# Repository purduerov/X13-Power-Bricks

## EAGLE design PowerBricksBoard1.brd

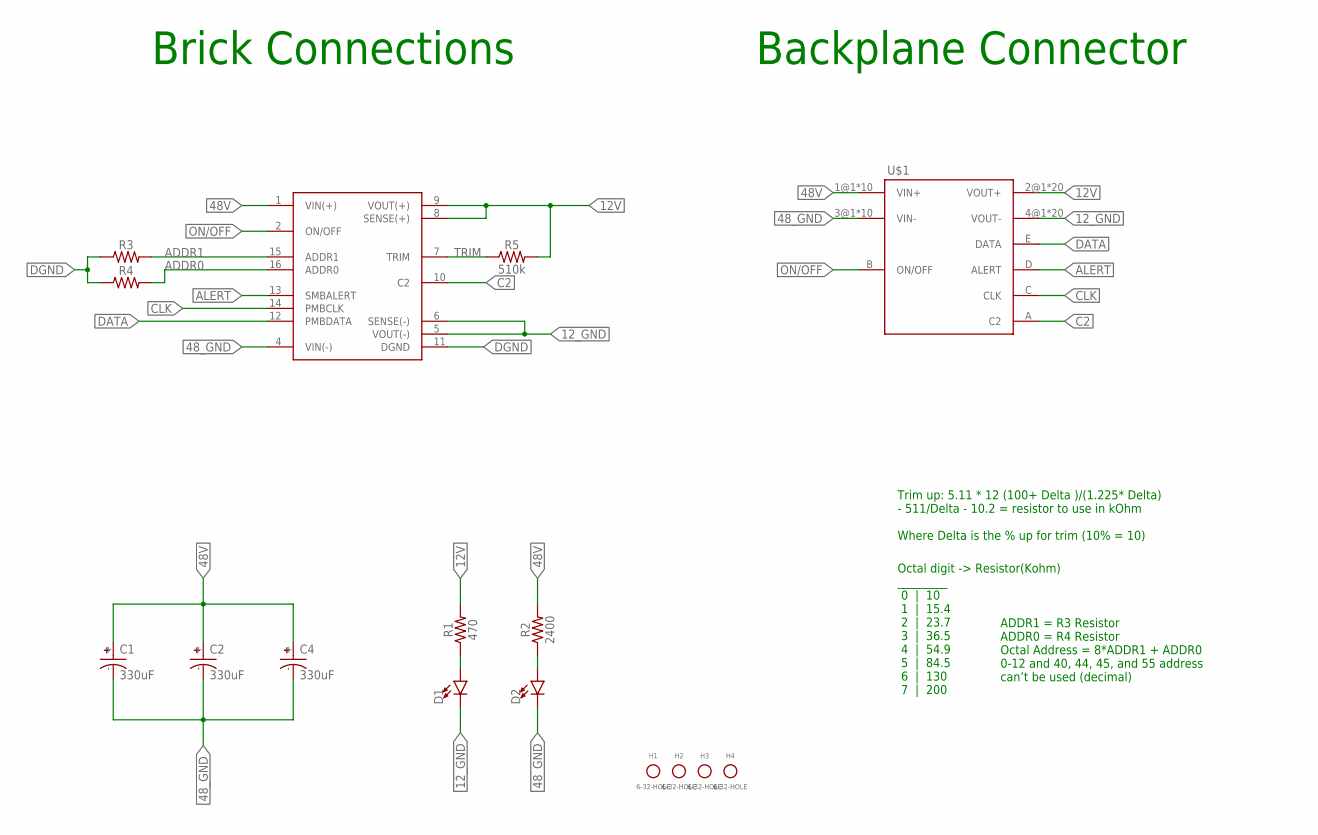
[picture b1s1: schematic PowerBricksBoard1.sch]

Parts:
C1, C2, C4: 330uF; CAPAE1030X1050N
D1, D2: LED0603; LED-0603
H1, H2, H3, H4: 6-32-HOLE
R1: 470; 0603
R2: 2400; 0603
R3, R4: 0603
R5: 510k; 0603
U$1: BRICK2DIST; BRICK2DIST_D2
U$2: Q48SC12050NRDH

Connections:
12V: R1.2, R5.2, U$1.2@1 (VOUT+), U$1.2@2 (VOUT+), U$1.2@3 (VOUT+), U$1.2@4 (VOUT+), U$1.2@5 (VOUT+), U$1.2@6 (VOUT+), U$1.2@7 (VOUT+), U$1.2@8 (VOUT+), U$1.2@9 (VOUT+), U$1.2@10 (VOUT+), U$1.2@11 (VOUT+), U$1.2@12 (VOUT+), U$1.2@13 (VOUT+), U$1.2@14 (VOUT+), U$1.2@15 (VOUT+), U$1.2@16 (VOUT+), U$1.2@17 (VOUT+), U$1.2@18 (VOUT+), U$1.2@19 (VOUT+), U$1.2@20 (VOUT+), U$2.8 (SENSE(+)), U$2.9 (VOUT(+))
12_GND: D1.C, U$1.4@1 (VOUT-), U$1.4@2 (VOUT-), U$1.4@3 (VOUT-), U$1.4@4 (VOUT-), U$1.4@5 (VOUT-), U$1.4@6 (VOUT-), U$1.4@7 (VOUT-), U$1.4@8 (VOUT-), U$1.4@9 (VOUT-), U$1.4@10 (VOUT-), U$1.4@11 (VOUT-), U$1.4@12 (VOUT-), U$1.4@13 (VOUT-), U$1.4@14 (VOUT-), U$1.4@15 (VOUT-), U$1.4@16 (VOUT-), U$1.4@17 (VOUT-), U$1.4@18 (VOUT-), U$1.4@19 (VOUT-), U$1.4@20 (VOUT-), U$2.5 (VOUT(-)), U$2.6 (SENSE(-))
48V: C1.+, C2.+, C4.+, R2.2, U$1.1@1 (VIN+), U$1.1@2 (VIN+), U$1.1@3 (VIN+), U$1.1@4 (VIN+), U$1.1@5 (VIN+), U$1.1@6 (VIN+), U$1.1@7 (VIN+), U$1.1@8 (VIN+), U$1.1@9 (VIN+), U$1.1@10 (VIN+), U$2.1 (VIN(+))
48_GND: C1.-, C2.-, C4.-, D2.C, U$1.3@1 (VIN-), U$1.3@2 (VIN-), U$1.3@3 (VIN-), U$1.3@4 (VIN-), U$1.3@5 (VIN-), U$1.3@6 (VIN-), U$1.3@7 (VIN-), U$1.3@8 (VIN-), U$1.3@9 (VIN-), U$1.3@10 (VIN-), U$2.4 (VIN(-))
ADDR0: R4.2, U$2.16 (ADDR0)
ADDR1: R3.2, U$2.15 (ADDR1)
ALERT: U$1.D (ALERT), U$2.13 (SMBALERT)
C2: U$1.A (C2), U$2.10 (C2)
CLK: U$1.C (CLK), U$2.14 (PMBCLK)
DATA: U$1.E (DATA), U$2.12 (PMBDATA)
DGND: R3.1, R4.1, U$2.11 (DGND)
unnamed: D1.A, R1.1
unnamed: D2.A, R2.1
ON/OFF: U$1.B (ON/OFF), U$2.2 (ON/OFF)
TRIM: R5.1, U$2.7 (TRIM)

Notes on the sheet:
Octal digit -> Resistor(Kohm) _________ 0 | 10 1 | 15.4 2 | 23.7 3 | 36.5 4 | 54.9 5 | 84.5 6 | 130 7 | 200
ADDR1 = R3 Resistor ADDR0 = R4 Resistor Octal Address = 8*ADDR1 + ADDR0 0-12 and 40, 44, 45, and 55 address can’t be used (decimal)
Brick Connections
Backplane Connector
Trim up: 5.11 * 12 (100+ Delta )/(1.225* Delta) - 511/Delta - 10.2 = resistor to use in kOhm Where Delta is the % up for trim (10% = 10)

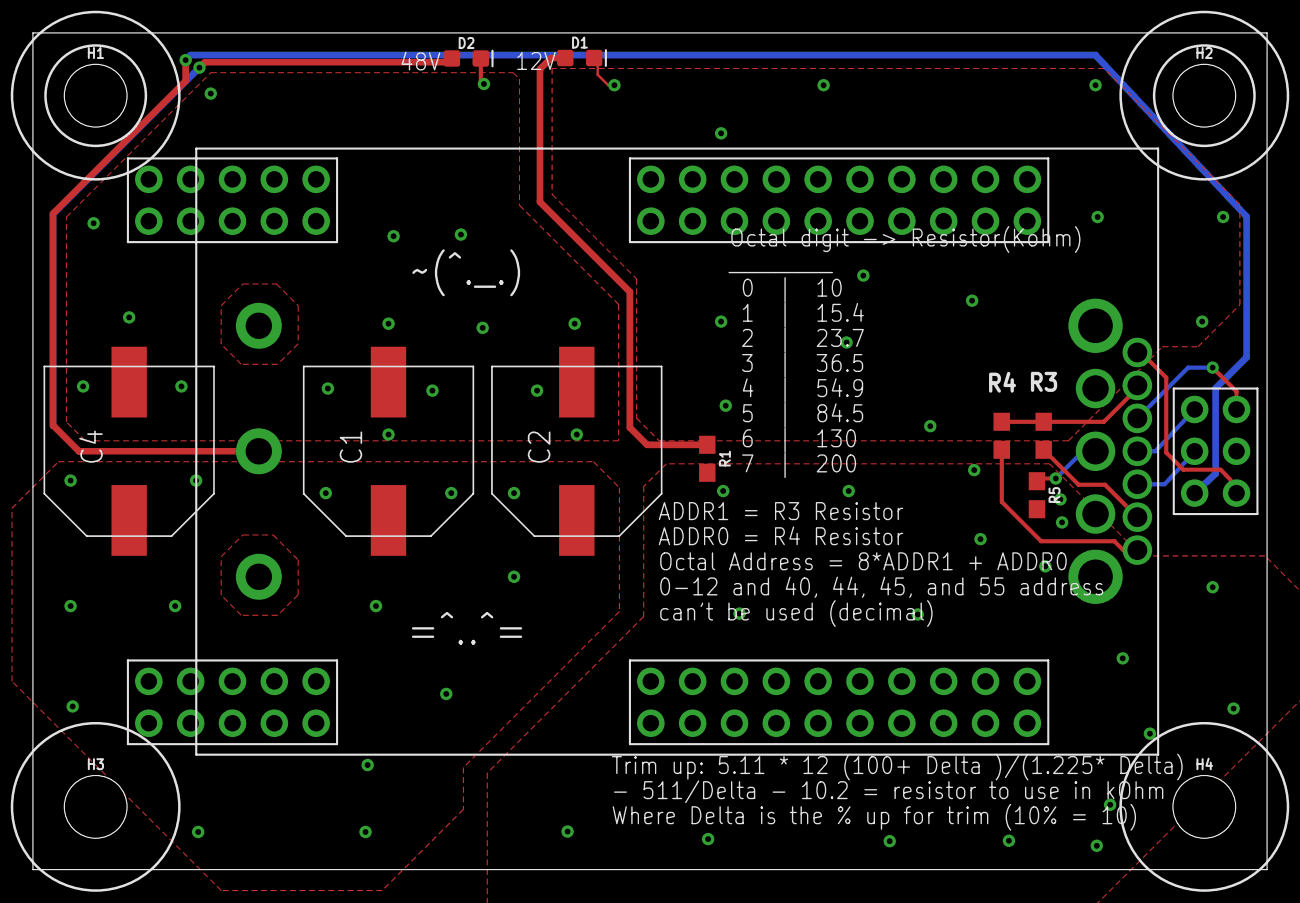
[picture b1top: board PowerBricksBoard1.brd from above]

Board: 2 copper layers, 74.9 x 50.8 mm, 16 parts (1 on the bottom side), 15 nets.

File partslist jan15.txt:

Partlist

Exported from PowerBricksBoard1.sch at 1/15/2021 2:06 PM

EAGLE Version 9.6.2 Copyright (c) 1988-2020 Autodesk, Inc.

Assembly variant: 

Part     Value          Device         Package         Library                             Sheet

C1       330uF          UCM1H331MNL1GS CAPAE1030X1050N brick-capacitor-UCM1H331MNL1GS      1
C2       330uF          UCM1H331MNL1GS CAPAE1030X1050N brick-capacitor-UCM1H331MNL1GS      1
C4       330uF          UCM1H331MNL1GS CAPAE1030X1050N brick-capacitor-UCM1H331MNL1GS      1
D1                      LED0603        LED-0603        SparkFun-LED                        1
D2                      LED0603        LED-0603        SparkFun-LED                        1
R1       470            RESISTOR0603   0603            SparkFun-Resistors                  1
R2       2400           RESISTOR0603   0603            SparkFun-Resistors                  1
R3                      RESISTOR0603   0603            SparkFun-Resistors                  1
R4                      RESISTOR0603   0603            SparkFun-Resistors                  1
R5       510k           RESISTOR0603   0603            SparkFun-Resistors                  1
U$1      BRICK2DIST     BRICK2DIST     BRICK2DIST_D2   Brick_Dist_Connector                1
U$2      Q48SC12050NRDH Q48SC12050NRDH Q48SC12050NRDH  Delta Power Bricks - Q48SC12050NRDH 1

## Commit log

2020-09-18 setup of repo
2020-10-14 x12 imported
2020-10-17 Updated power bricks board with polarized capacitor schematic symbol
2020-10-17 Updated board w/ latest x12 update, otherwise same as before
2020-10-24 part
2020-10-25 remove library files and X12 board
2020-10-31 board
2020-10-31 layout
2020-10-31 power plane polygons routed, board layout set. Schematic and IO work remains as well as the octa table
2020-10-31 planes: good
2020-11-07 schematic update in 2 days (in valve time)
2020-11-07 schematic, resistor calcs, routing
2020-11-14 latest
2020-11-21 yes these changes are very pog
2020-12-03 brick update
2020-12-05 test
2020-12-05 Ready for design review
2020-12-05 final
2021-01-02 cad placement for tyler (routing not done)
2021-01-02 hi i updated it
2021-01-07 Done but I still need to add a picture Owo
2021-01-09 trim
2021-01-10 Cleaning up git and exports for order
2021-01-11 shrunk 0.025
2021-01-11 50mil smol
2021-01-11 Revert "trim"
    This reverts commit 0055e3f947d82e2e184832a38c8fbe8e78d74489.
2021-01-11 Revert "Revert "trim""
    This reverts commit 46b5d4a1c2a012013371b894087438f3b54206c6.
2021-01-11 step for shrunk brick
2021-01-11 step for shrunk brick and board text
2021-12-02 euhreiuhthjtrgrefwefrgyjgr

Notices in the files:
parts and their libraries:
SparkFun-LED: Licensing: Creative Commons ShareAlike 4.0 International - https://creativecommons.org/licenses/by-sa/4.0
